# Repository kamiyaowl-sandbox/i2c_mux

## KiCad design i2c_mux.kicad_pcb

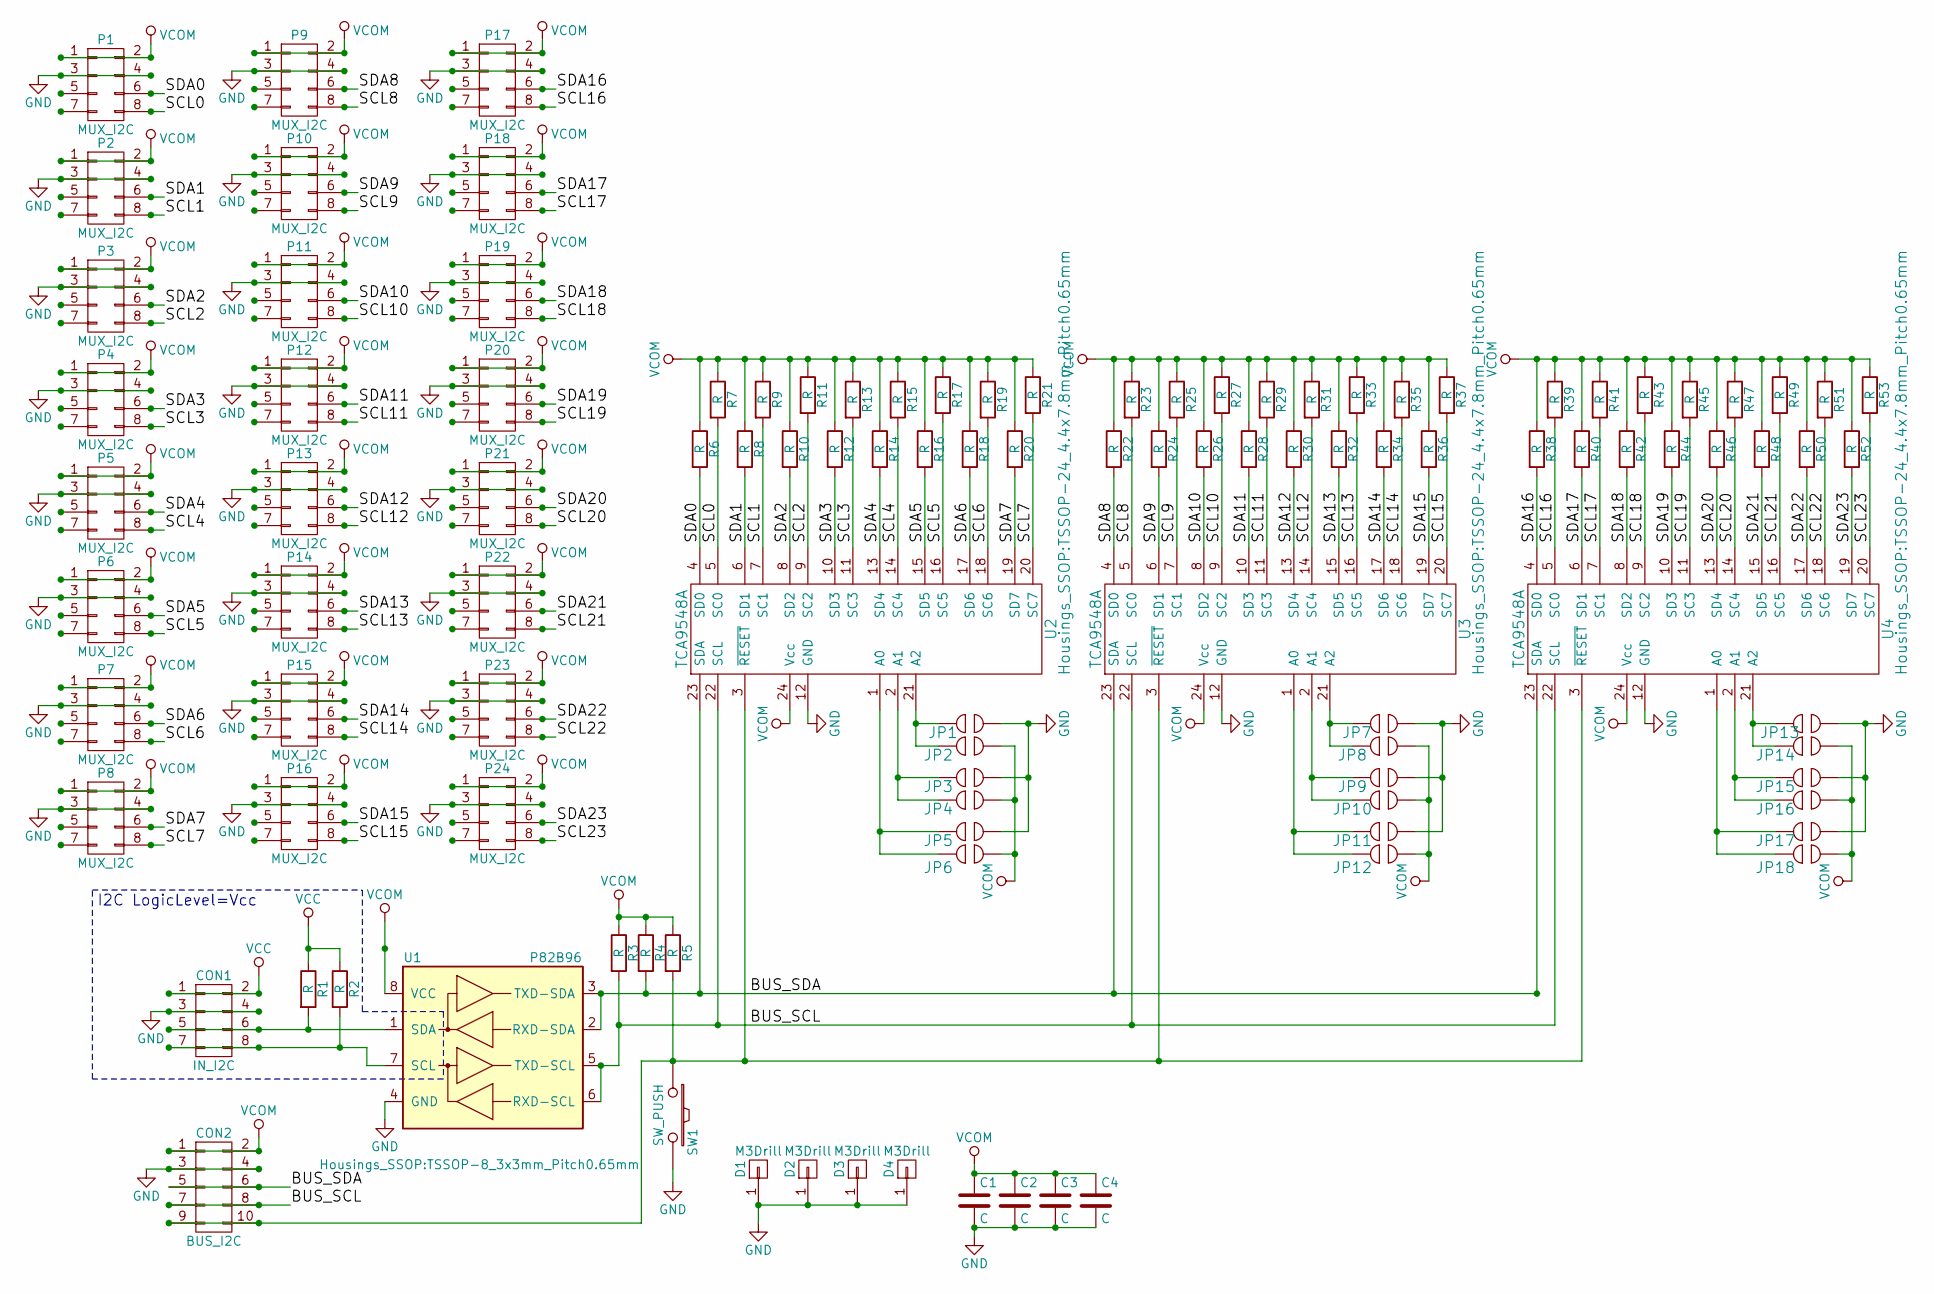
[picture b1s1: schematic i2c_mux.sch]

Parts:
C1, C2, C3, C4: C; C_0603_HandSoldering
CON1: IN_I2C; Pin_Header_Straight_2x04
CON2: BUS_I2C; Pin_Header_Straight_2x05
D1, D2, D3, D4: M3Drill; M3_Drill
JP1, JP2, JP3, JP4, JP5, JP6, JP7, JP8, JP9, JP10, JP11, JP12, JP13, JP14, JP15, JP16, JP17, JP18: UserShort
P1, P2, P3, P4, P5, P6, P7, P8, P9, P10, P11, P12, P13, P14, P15, P16, P17, P18, P19, P20, P21, P22, P23, P24: MUX_I2C; Pin_Header_Straight_2x04
R1, R2, R3, R4, R5, R6, R7, R8, R9, R10, R11, R12, R13, R14, R15, R16, R17, R18, R19, R20, R21, R22, R23, R24, R25, R26, R27, R28, R29, R30, R31, R32, R33, R34, R35, R36, R37, R38, R39, R40, R41, R42, R43, R44, R45, R46, R47, R48, R49, R50, R51, R52, R53: R; R_0603_HandSoldering
SW1: SW_PUSH; ALPS_SW_SKRPACE010
U1: P82B96; TSSOP-8_3x3mm_Pitch0.65mm
U2, U3, U4: TCA9548A; TSSOP-24_4.4x7.8mm_Pitch0.65mm

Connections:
/BUS_SCL: CON2.7, CON2.8, R3.2, U1.5 (TXD-SCL), U1.6 (RXD-SCL), U2.22 (SCL), U3.22 (SCL), U4.22 (SCL)
/BUS_SDA: CON2.5, CON2.6, R4.2, U1.2 (RXD-SDA), U1.3 (TXD-SDA), U2.23 (SDA), U3.23 (SDA), U4.23 (SDA)
/SCL0: P1.8, R7.2, U2.5 (SC0)
/SCL1: P2.8, R9.2, U2.7 (SC1)
/SCL2: P3.8, R11.2, U2.9 (SC2)
/SCL3: P4.8, R13.2, U2.11 (SC3)
/SCL4: P5.8, R15.2, U2.14 (SC4)
/SCL5: P6.8, R17.2, U2.16 (SC5)
/SCL6: P7.8, R19.2, U2.18 (SC6)
/SCL7: P8.8, R21.2, U2.20 (SC7)
/SCL8: P9.8, R23.2, U3.5 (SC0)
/SCL9: P10.8, R25.2, U3.7 (SC1)
/SCL10: P11.8, R27.2, U3.9 (SC2)
/SCL11: P12.8, R29.2, U3.11 (SC3)
/SCL12: P13.8, R31.2, U3.14 (SC4)
/SCL13: P14.8, R33.2, U3.16 (SC5)
/SCL14: P15.8, R35.2, U3.18 (SC6)
/SCL15: P16.8, R37.2, U3.20 (SC7)
/SCL16: P17.8, R39.2, U4.5 (SC0)
/SCL17: P18.8, R41.2, U4.7 (SC1)
/SCL18: P19.8, R43.2, U4.9 (SC2)
/SCL19: P20.8, R45.2, U4.11 (SC3)
/SCL20: P21.8, R47.2, U4.14 (SC4)
/SCL21: P22.8, R49.2, U4.16 (SC5)
/SCL22: P23.8, R51.2, U4.18 (SC6)
/SCL23: P24.8, R53.2, U4.20 (SC7)
/SDA0: P1.6, R6.2, U2.4 (SD0)
/SDA1: P2.6, R8.2, U2.6 (SD1)
/SDA2: P3.6, R10.2, U2.8 (SD2)
/SDA3: P4.6, R12.2, U2.10 (SD3)
/SDA4: P5.6, R14.2, U2.13 (SD4)
/SDA5: P6.6, R16.2, U2.15 (SD5)
/SDA6: P7.6, R18.2, U2.17 (SD6)
/SDA7: P8.6, R20.2, U2.19 (SD7)
/SDA8: P9.6, R22.2, U3.4 (SD0)
/SDA9: P10.6, R24.2, U3.6 (SD1)
/SDA10: P11.6, R26.2, U3.8 (SD2)
/SDA11: P12.6, R28.2, U3.10 (SD3)
/SDA12: P13.6, R30.2, U3.13 (SD4)
/SDA13: P14.6, R32.2, U3.15 (SD5)
/SDA14: P15.6, R34.2, U3.17 (SD6)
/SDA15: P16.6, R36.2, U3.19 (SD7)
/SDA16: P17.6, R38.2, U4.4 (SD0)
/SDA17: P18.6, R40.2, U4.6 (SD1)
/SDA18: P19.6, R42.2, U4.8 (SD2)
/SDA19: P20.6, R44.2, U4.10 (SD3)
/SDA20: P21.6, R46.2, U4.13 (SD4)
/SDA21: P22.6, R48.2, U4.15 (SD5)
/SDA22: P23.6, R50.2, U4.17 (SD6)
/SDA23: P24.6, R52.2, U4.19 (SD7)
GND: C1.2, C2.2, C3.2, C4.2, CON1.3, CON1.4, CON2.3, CON2.4, D1.1, D2.1, D3.1, D4.1, JP1.2, JP3.2, JP5.2, JP7.2, JP9.2, JP11.2, JP13.2, JP15.2, JP17.2, P1.3, P1.4, P2.3, P2.4, P3.3, P3.4, P4.3, P4.4, P5.3, P5.4, P6.3, P6.4, P7.3, P7.4, P8.3, P8.4, P9.3, P9.4, P10.3, P10.4, P11.3, P11.4, P12.3, P12.4, P13.3, P13.4, P14.3, P14.4, P15.3, P15.4, P16.3, P16.4, P17.3, P17.4, P18.3, P18.4, P19.3, P19.4, P20.3, P20.4, P21.3, P21.4, P22.3, P22.4, P23.3, P23.4, P24.3, P24.4, SW1.2, U1.4 (GND), U2.12 (GND), U3.12 (GND), U4.12 (GND)
unnamed: CON1.5, CON1.6, R1.2, U1.1 (SDA)
unnamed: CON1.7, CON1.8, R2.2, U1.7 (SCL)
unnamed: CON2.9, CON2.10, R5.2, SW1.1, U2.3 (~RESET), U3.3 (~RESET), U4.3 (~RESET)
unnamed: JP1.1, JP2.1, U2.21 (A2)
unnamed: JP3.1, JP4.1, U2.2 (A1)
unnamed: JP5.1, JP6.1, U2.1 (A0)
unnamed: JP7.1, JP8.1, U3.21 (A2)
unnamed: JP9.1, JP10.1, U3.2 (A1)
unnamed: JP11.1, JP12.1, U3.1 (A0)
unnamed: JP13.1, JP14.1, U4.21 (A2)
unnamed: JP15.1, JP16.1, U4.2 (A1)
unnamed: JP17.1, JP18.1, U4.1 (A0)
VCC: CON1.1, CON1.2, R1.1, R2.1
VCOM: C1.1, C2.1, C3.1, C4.1, CON2.1, CON2.2, JP2.2, JP4.2, JP6.2, JP8.2, JP10.2, JP12.2, JP14.2, JP16.2, JP18.2, P1.1, P1.2, P2.1, P2.2, P3.1, P3.2, P4.1, P4.2, P5.1, P5.2, P6.1, P6.2, P7.1, P7.2, P8.1, P8.2, P9.1, P9.2, P10.1, P10.2, P11.1, P11.2, P12.1, P12.2, P13.1, P13.2, P14.1, P14.2, P15.1, P15.2, P16.1, P16.2, P17.1, P17.2, P18.1, P18.2, P19.1, P19.2, P20.1, P20.2, P21.1, P21.2, P22.1, P22.2, P23.1, P23.2, P24.1, P24.2, R3.1, R4.1, R5.1, R6.1, R7.1, R8.1, R9.1, R10.1, R11.1, R12.1, R13.1, R14.1, R15.1, R16.1, R17.1, R18.1, R19.1, R20.1, R21.1, R22.1, R23.1, R24.1, R25.1, R26.1, R27.1, R28.1, R29.1, R30.1, R31.1, R32.1, R33.1, R34.1, R35.1, R36.1, R37.1, R38.1, R39.1, R40.1, R41.1, R42.1, R43.1, R44.1, R45.1, R46.1, R47.1, R48.1, R49.1, R50.1, R51.1, R52.1, R53.1, U1.8 (VCC), U2.24 (Vcc), U3.24 (Vcc), U4.24 (Vcc)

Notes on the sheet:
I2C LogicLevel=Vcc

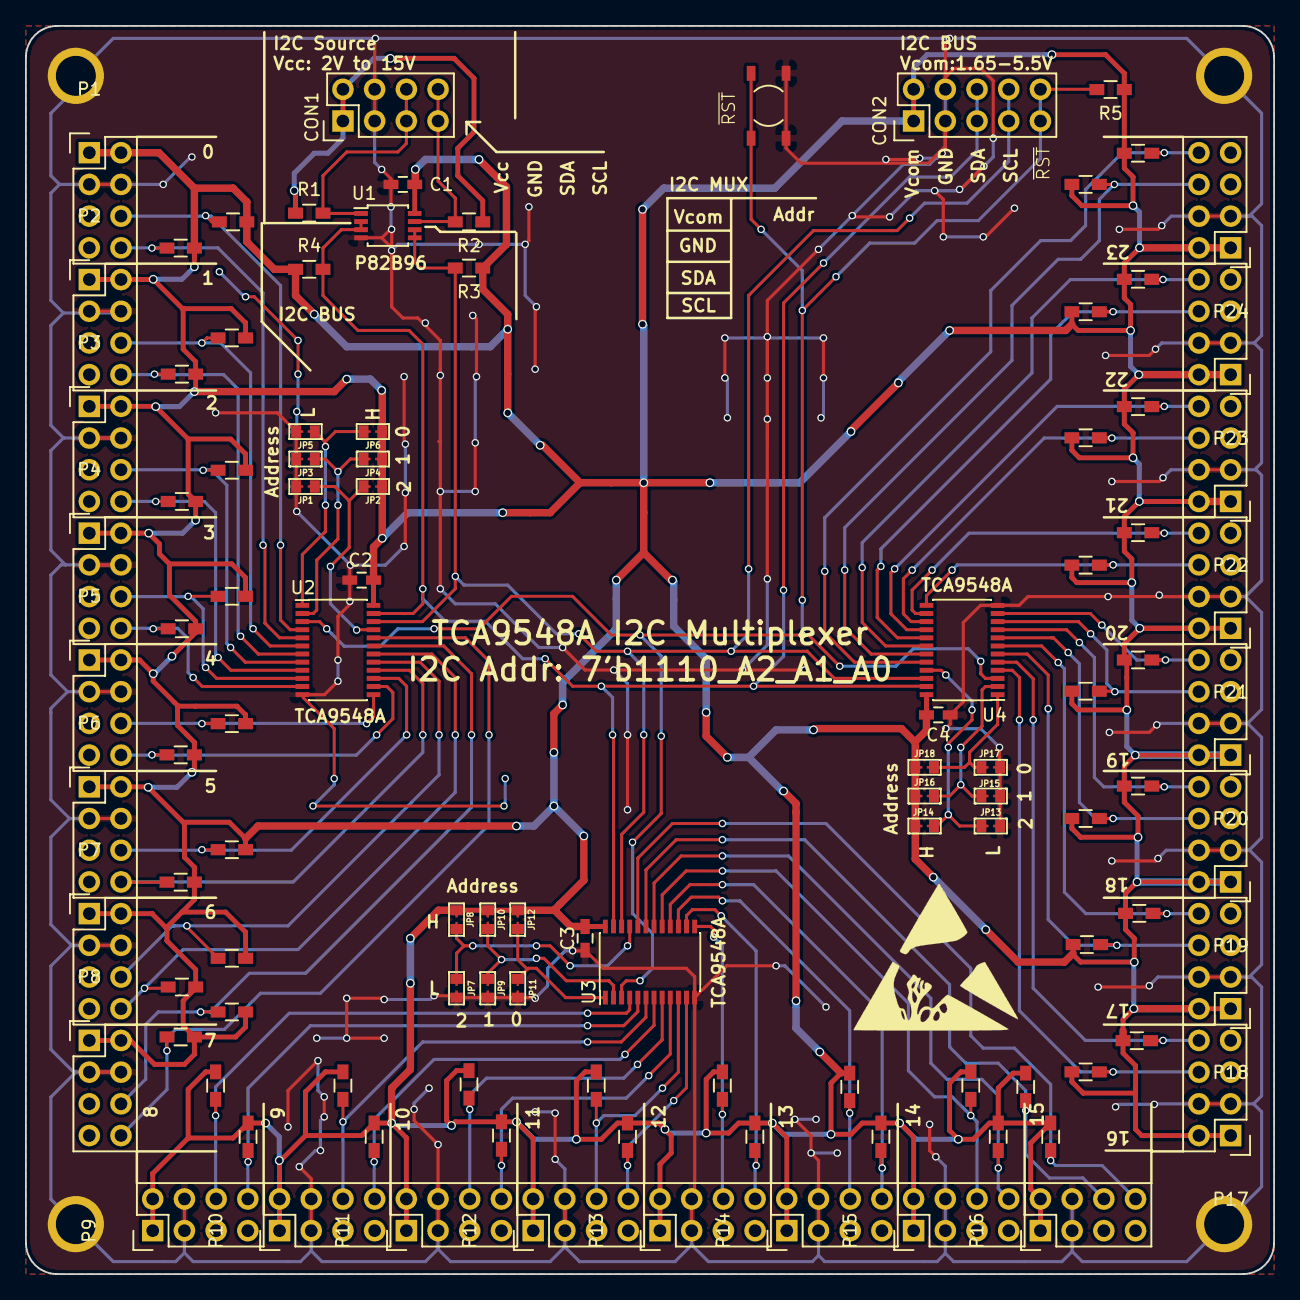
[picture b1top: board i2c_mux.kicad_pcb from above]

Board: 2 copper layers, 100.0 x 100.0 mm, 110 parts (0 on the bottom side), 65 nets.
